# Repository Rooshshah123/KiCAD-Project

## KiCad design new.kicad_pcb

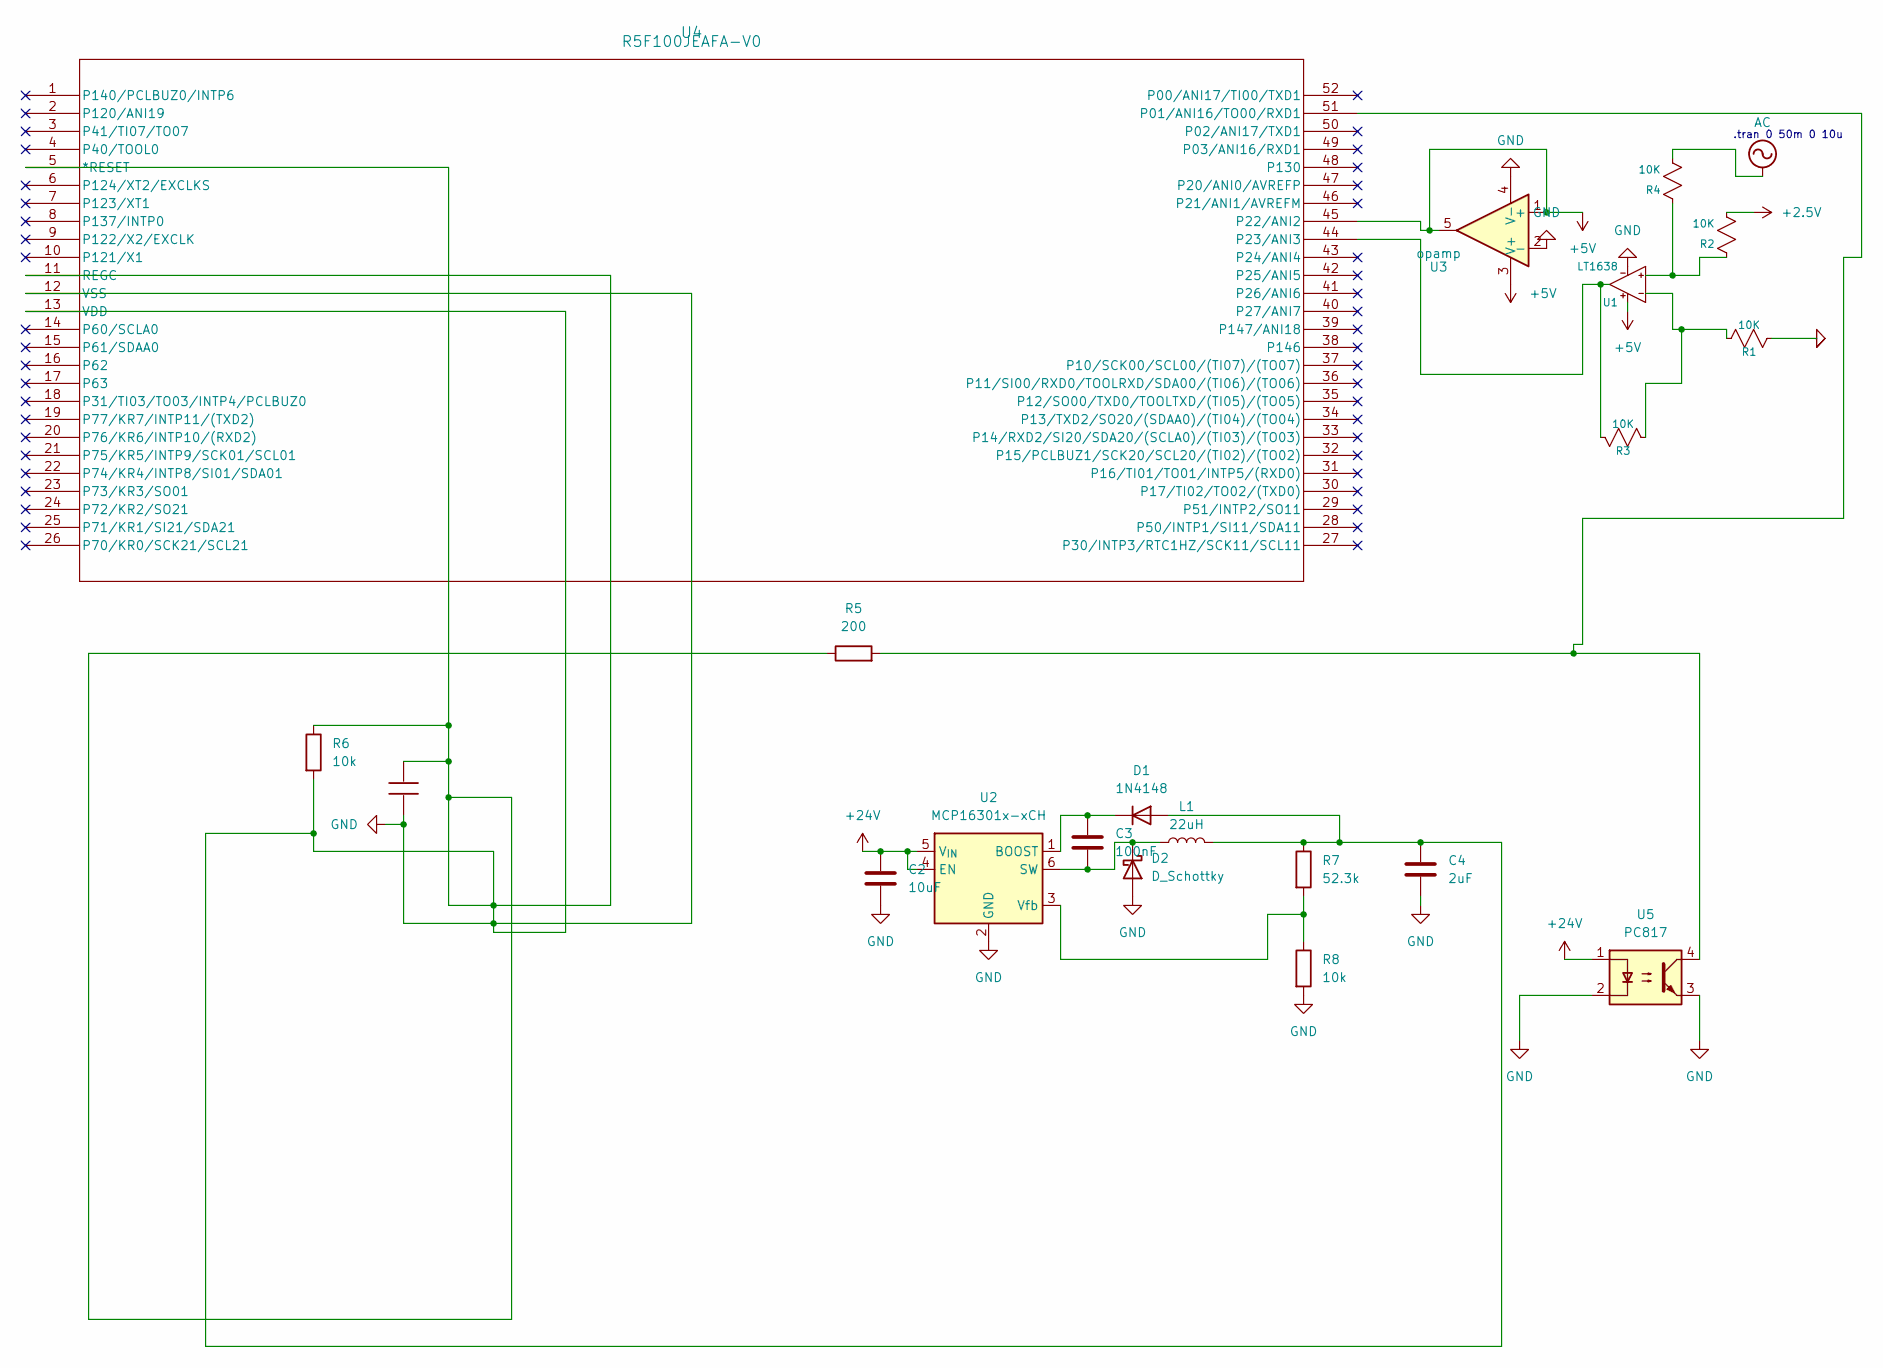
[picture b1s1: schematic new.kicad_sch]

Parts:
C1: 1uF; C_Axial_L3.8mm_D2.6mm_P7.50mm_Horizontal
C2: 10uF; C_Axial_L3.8mm_D2.6mm_P7.50mm_Horizontal
C3: 100nF; C_Axial_L3.8mm_D2.6mm_P7.50mm_Horizontal
C4: 2uF; C_Axial_L3.8mm_D2.6mm_P7.50mm_Horizontal
D1: 1N4148; D_DO-35_SOD27_P7.62mm_Horizontal
D2: D_Schottky; D_DO-41_SOD81_P3.81mm_Vertical_AnodeUp
L1: 22uH; L_Axial_L5.0mm_D3.6mm_P10.00mm_Horizontal_Murata_BL01RN1A2A2
R1, R2, R3, R4: 10K; R_Axial_DIN0204_L3.6mm_D1.6mm_P1.90mm_Vertical
R5: 200; R_Axial_DIN0204_L3.6mm_D1.6mm_P1.90mm_Vertical
R6, R8: 10k; R_Axial_DIN0204_L3.6mm_D1.6mm_P1.90mm_Vertical
R7: 52.3k; R_Axial_DIN0204_L3.6mm_D1.6mm_P1.90mm_Vertical
U1: LT1638; lt1638
U2: MCP16301x-xCH; SOT-23-6
U3: opamp; lt1638
U4: R5F100JEAFA-V0; LQFP52_REN-M
U5: PC817; DIL04

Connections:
0: R1.2
+2.5V: R2.2
+5V: U1.3 (V+), U3.1 (+), U3.3 (V+), U3.5, U4.45 (P22/ANI2)
+24V: C2.1, U2.4 (EN), U2.5 (V_{IN}), U5.1
AC: R4.2
GND: C1.1, C1.2, C2.2, C4.1, C4.2, D1.2 (A), D2.2 (A), L1.2, R5.1, R6.1, R6.2, R7.1, R8.2, U1.4 (V-), U2.2 (GND), U3.2 (-), U3.4 (V-), U4.5 (*RESET), U4.11 (REGC), U4.12 (VSS), U4.13 (VDD), U5.2, U5.3
unnamed: C3.1, D1.1 (K), U2.1 (BOOST)
unnamed: C3.2, D2.1 (K), L1.1, U2.6 (SW)
unnamed: R2.1, R4.1, U1.1 (In+)
unnamed: R1.1, R3.2, U1.2 (In-)
unnamed: R3.1, U1.5 (OUT), U4.44 (P23/ANI3)
unnamed: R7.2, R8.1, U2.3 (Vfb)
unnamed: R5.2, U4.51 (P01/ANI16/TO00/RXD1), U5.4

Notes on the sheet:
.tran 0 50m 0 10u

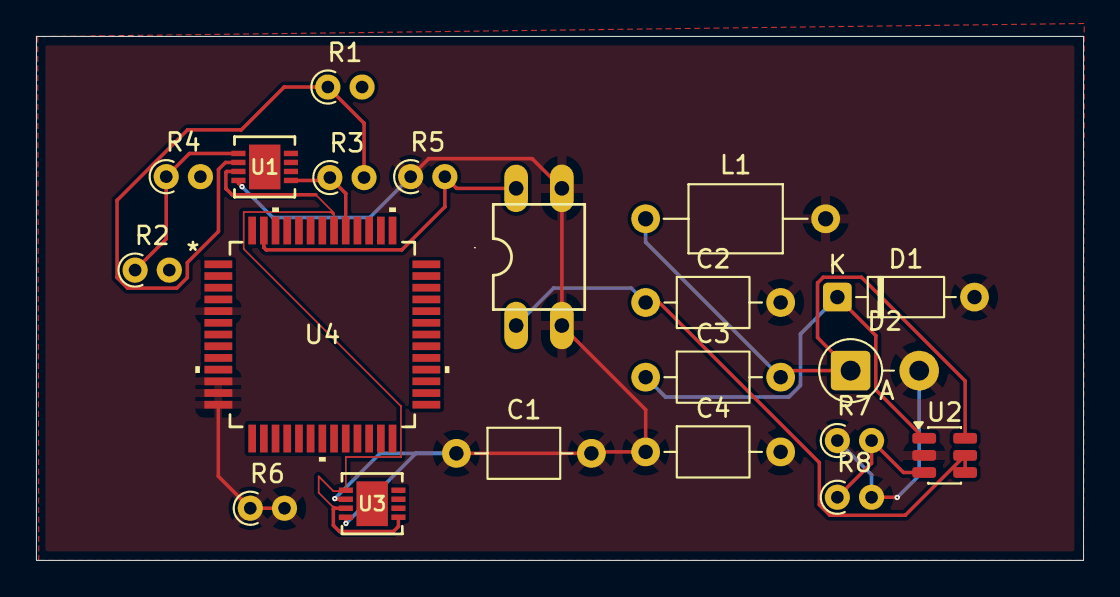
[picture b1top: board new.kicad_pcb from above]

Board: 2 copper layers, 58.2 x 29.1 mm, 20 parts (0 on the bottom side), 10 nets.

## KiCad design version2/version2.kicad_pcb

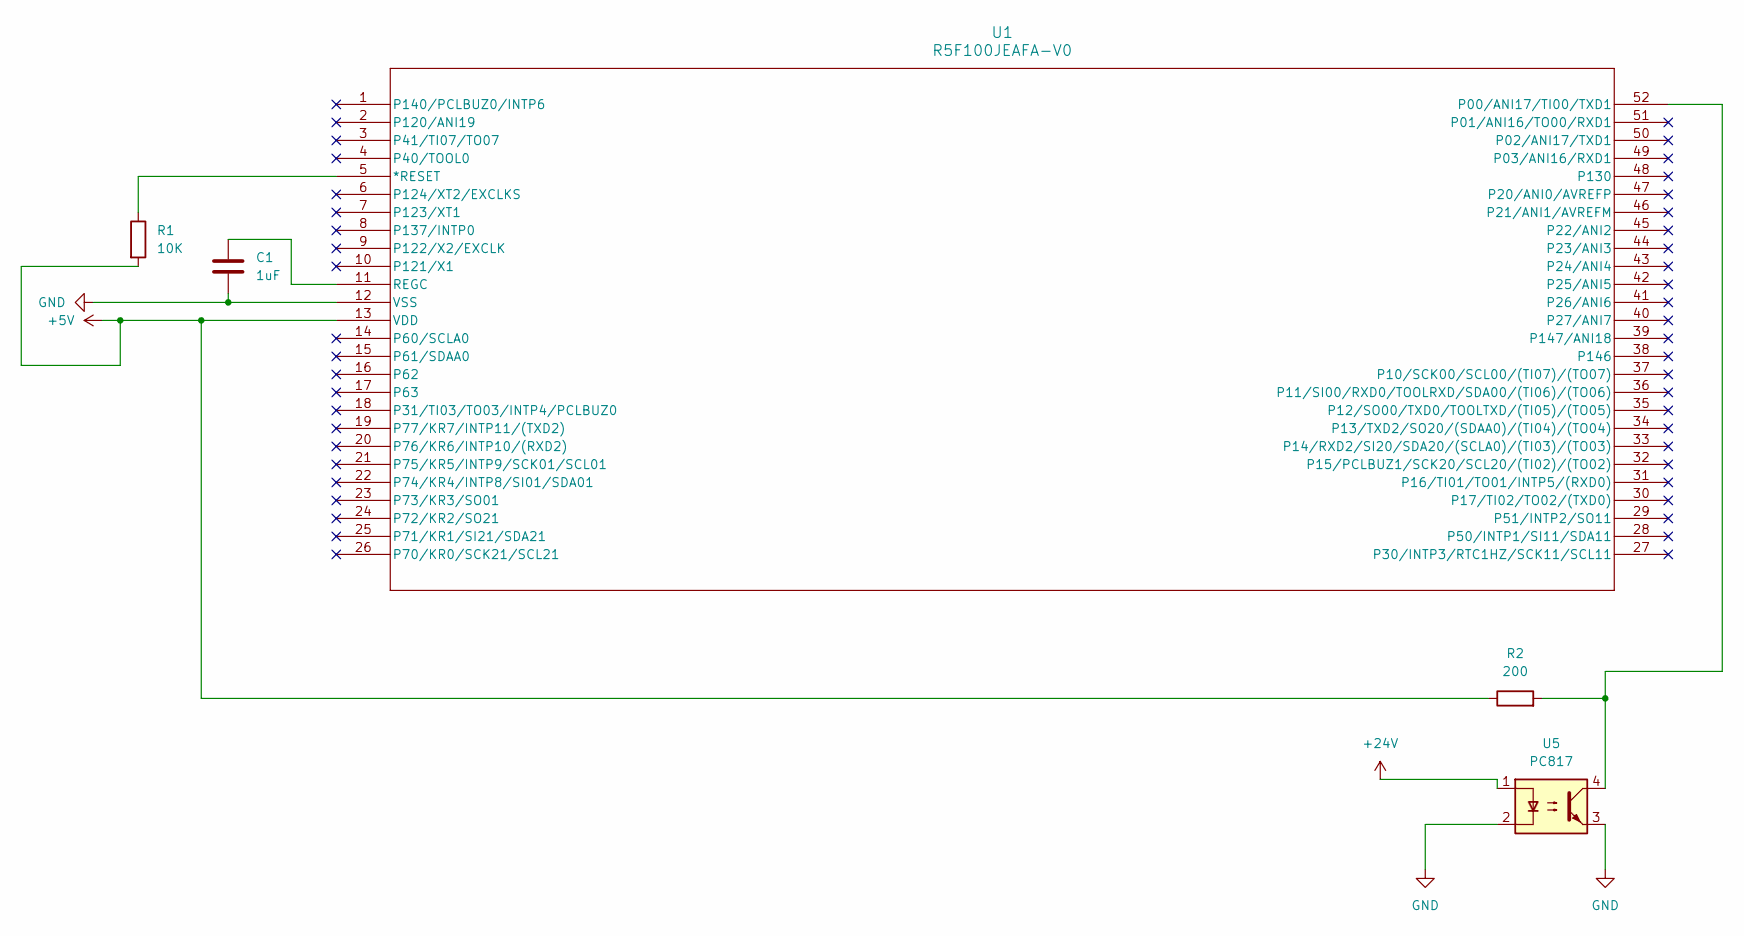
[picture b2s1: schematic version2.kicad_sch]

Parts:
C1: 1uF; C_Disc_D3.0mm_W1.6mm_P2.50mm
R1: 10K; R_Axial_DIN0204_L3.6mm_D1.6mm_P5.08mm_Horizontal
R2: 200; R_Axial_DIN0204_L3.6mm_D1.6mm_P5.08mm_Horizontal
U1: R5F100JEAFA-V0; LQFP52_REN-M
U5: PC817; DIL04

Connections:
+5V: R1.2, R2.1, U1.13 (VDD)
+24V: U5.1
GND: C1.2, U1.12 (VSS), U5.2, U5.3
unnamed: R1.1, U1.5 (*RESET)
unnamed: R2.2, U1.52 (P00/ANI17/TI00/TXD1), U5.4
unnamed: C1.1, U1.11 (REGC)

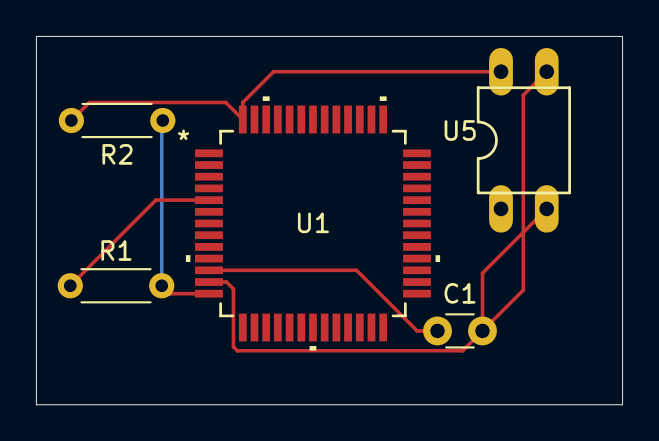
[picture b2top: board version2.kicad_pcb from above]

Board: 2 copper layers, 32.6 x 20.5 mm, 5 parts (0 on the bottom side), 5 nets.

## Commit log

2026-03-12 final output of voltage gerber file
